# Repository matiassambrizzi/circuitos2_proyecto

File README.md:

#Amplificador Clase H/G

#test

#Para hacer por unica vez:

#echo "# algo2_tp1" >> README.md

#git init

#git add README.md

#git commit -m "first commit"

#git remote add origin https://github.com/matiassambrizzi/circuitos2_proyecto.git

#git push -u origin master

#Para que se guarde la contra

#git config credential.helper store

#git push https://github.com/matiassambrizzi/circuitos2_proyecto.git

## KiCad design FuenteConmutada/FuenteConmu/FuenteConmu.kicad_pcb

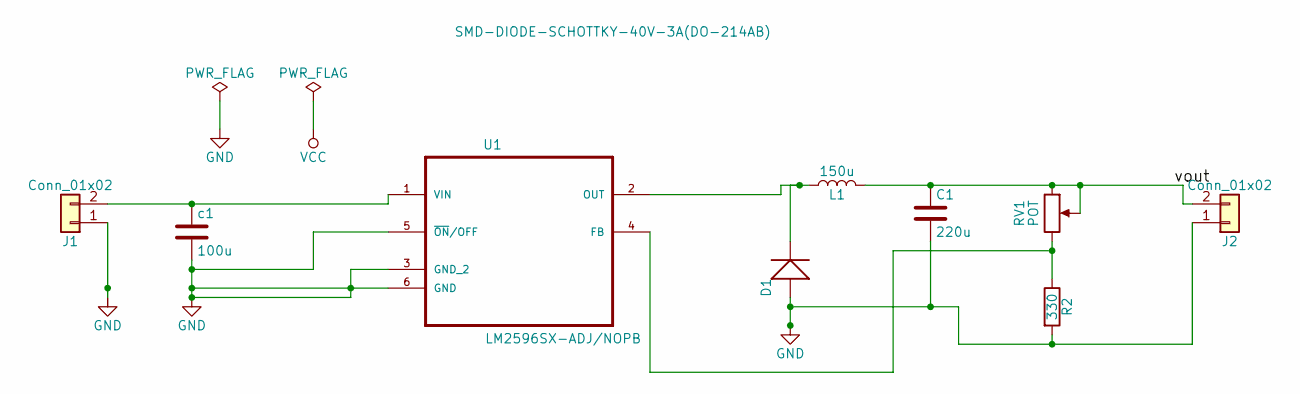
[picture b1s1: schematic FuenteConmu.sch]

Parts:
C1: 220u; CP_Radial_D4.0mm_P1.50mm
D1: SMD-DIODE-SCHOTTKY-40V-3A(DO-214AB); DO-214AB
J1, J2: Conn_01x02; PINHEAD1-2
L1: 150u; L_12x12mm_h8mm
R2: 330; R_0201
RV1: POT; TRIM_3296W-1-250
U1: LM2596SX-ADJ/NOPB; TO170P1435X465-6N
c1: 100u; CP_Radial_D4.0mm_P1.50mm

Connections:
/vout: C1.1, J2.2, L1.2, RV1.1, RV1.2
GND: C1.2, D1.1 (+), J1.1, J2.1, R2.2, U1.3 (GND_2), U1.5 (~ON~/OFF), U1.6 (GND), c1.2
unnamed: D1.2 (-), L1.1, U1.2 (OUT)
unnamed: J1.2, U1.1 (VIN), c1.1
unnamed: R2.1, RV1.3, U1.4 (FB)

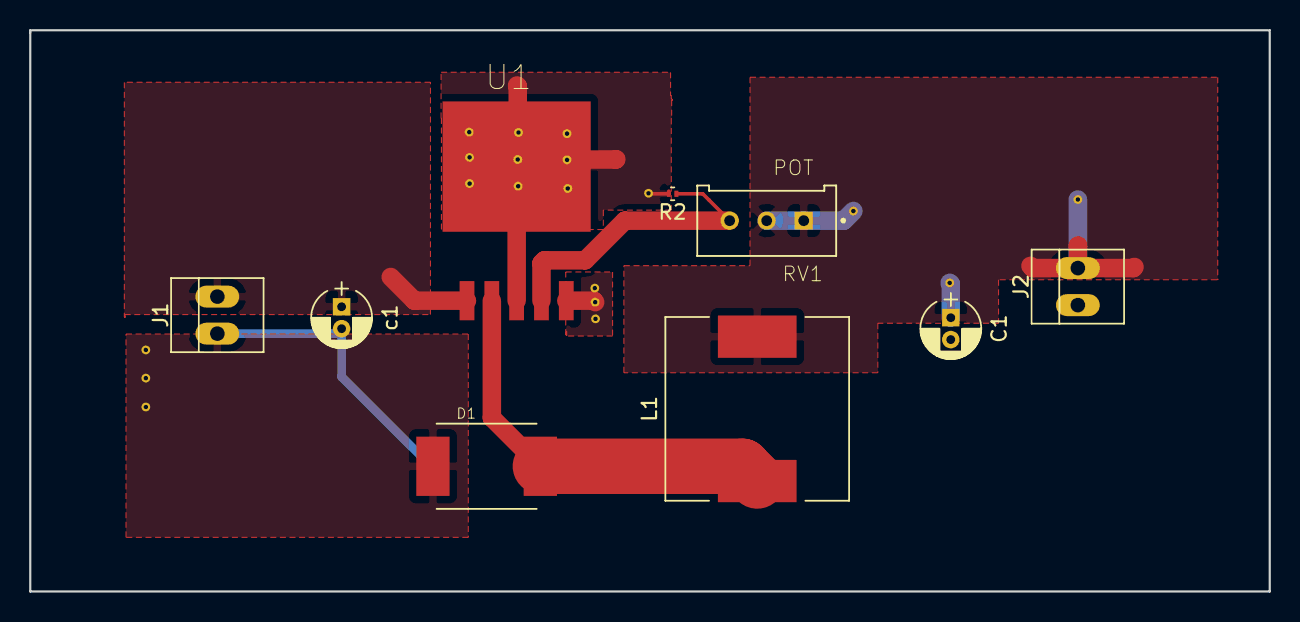
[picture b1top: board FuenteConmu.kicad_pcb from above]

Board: 2 copper layers, 85.0 x 38.5 mm, 9 parts (0 on the bottom side), 5 nets.

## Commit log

2018-11-03 sarasa
2018-11-03 Cosas
2018-11-03 Simulaciones que hicimos el viernes 2/11
2018-11-03 Simulaciones
2018-11-10 Circuito del douglas
2018-11-10 Borro los .raw
2018-11-10 algunas modif
2018-11-12 Chequear estos cambios
2018-11-14 add: Etapa de salida
2018-11-14 Ordeno un cacho las carpetas
2018-11-14 Argego etapa de saldia a IntentoDeEtapaDeEntrada
2018-11-15 Agrego los circuitos de ejemplo
2018-11-15 Algunas datasheets
2018-11-15 Ordenamiento
2018-11-15 Simulando copmaradores
2018-11-15 prueba
2018-11-15 Ultimas
2018-11-22 BubbleSort
2018-11-22 InsertionSort
2018-11-23 SelectionSort
2019-05-07 Cambios
